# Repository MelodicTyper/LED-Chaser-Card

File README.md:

# LED Chasing Board
Little PCB that has an LED chaser circuit. The leds should "chase" each other around, and you can change brightness (and I think speed) from the potentiometer. 

I based this off of a flip flop circuit I saw online. I took that design, added a third "flip flop" to it, and added a potentiometer. From there, I designed the PCB and tested it.

For this project, I used 3 capacitors (10uf), 6 resistors (3 220ohm and 3 4.7kohm), 3 leds, 3 NPN transitors, a potentiometer, and a battery holder! Detailed Bill of Materials in the repo.

For verification for HackClub Solder YSWS (http://solder.hackclub.com/), my slack username is Melodic.

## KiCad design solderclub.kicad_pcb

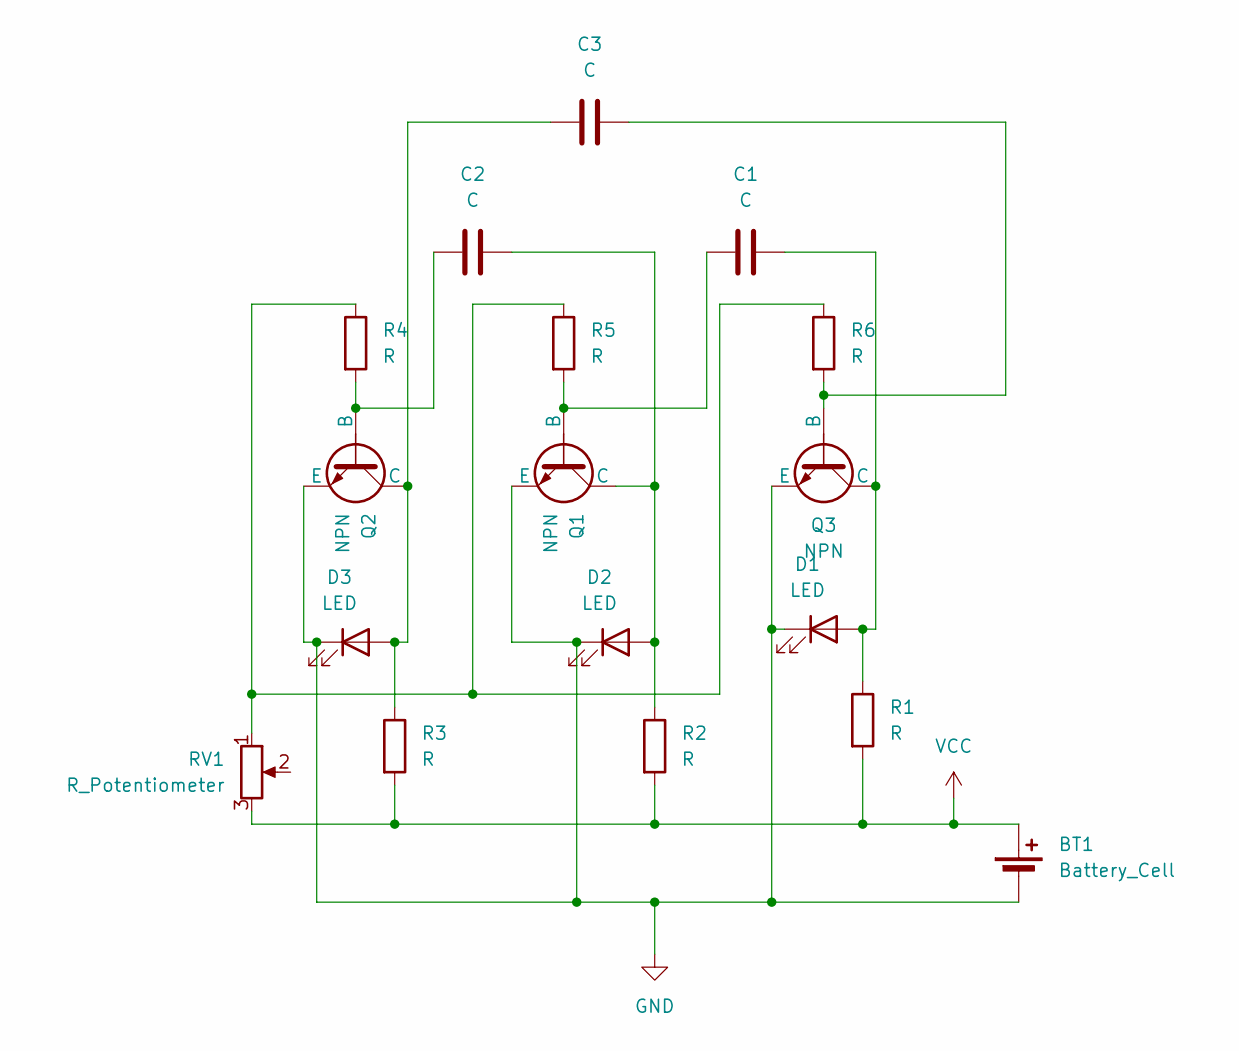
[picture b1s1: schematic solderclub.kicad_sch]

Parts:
BT1: Battery_Cell; BatteryHolder_Keystone_3034_1x20mm
C1, C2, C3: C; CP_Radial_D8.0mm_P5.00mm
D1, D2, D3: LED; LED_D5.0mm
Q1, Q2, Q3: NPN; TO-92L_HandSolder
R1, R2, R3, R4, R5, R6: R; R_Axial_DIN0207_L6.3mm_D2.5mm_P7.62mm_Horizontal
RV1: R_Potentiometer; Potentiometer_Vishay_T73YP_Vertical

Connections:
GND: BT1.2 (-), D1.1 (K), D2.1 (K), D3.1 (K), Q1.3 (E), Q2.3 (E), Q3.3 (E)
unnamed: C1.1, D1.2 (A), Q3.1 (C), R1.1
unnamed: C2.2, D2.2 (A), Q1.1 (C), R2.1
unnamed: C3.2, D3.2 (A), Q2.1 (C), R3.1
unnamed: C1.2, Q1.2 (B), R5.2
unnamed: C2.1, Q2.2 (B), R4.2
unnamed: C3.1, Q3.2 (B), R6.2
unnamed: R4.1, R5.1, R6.1, RV1.1
VCC: BT1.1 (+), R1.2, R2.2, R3.2, RV1.3

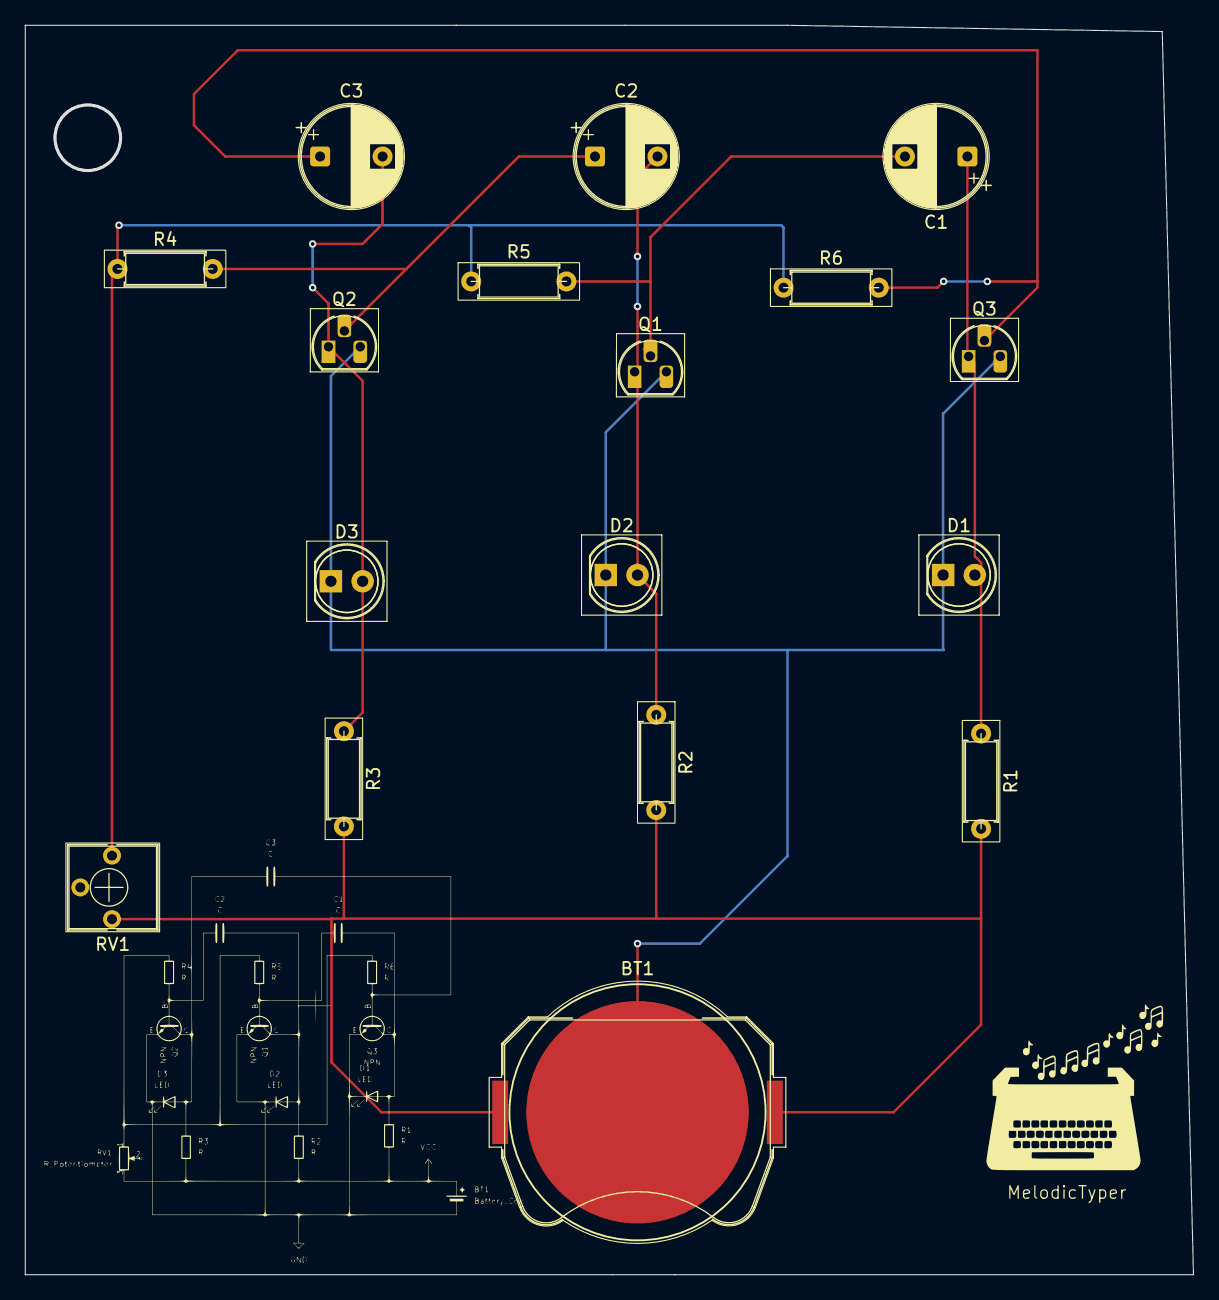
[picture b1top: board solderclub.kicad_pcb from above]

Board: 2 copper layers, 93.5 x 100.0 mm, 17 parts (0 on the bottom side), 9 nets.

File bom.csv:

Designator,Footprint,Quantity,Value,LCSC Part #
BT1,BatteryHolder_Keystone_3034_1x20mm,1,Battery_Cell,
"C1, C2, C3",CP_Radial_D8.0mm_P5.00mm,3,C,
"D1, D2, D3",LED_D5.0mm,3,LED,
"Q1, Q2, Q3",TO-92L_HandSolder,3,NPN,
"R1, R2, R3, R4, R5, R6",R_Axial_DIN0207_L6.3mm_D2.5mm_P7.62mm_Horizontal,6,R,
RV1,Potentiometer_Vishay_T73YP_Vertical,1,R_Potentiometer,

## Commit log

2025-06-30 Production files
